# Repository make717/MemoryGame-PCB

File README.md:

# MemoryGame-PCB
KiCad PCB files for custom [Make717 memory game](https://github.com/make717gh/MemoryGame) soldering badge. This badge was designed and built by members of [Make717](https://www.make717.org) for a soldering event at the [Lancaster Science Factory](https://www.lancastersciencefactory.org/) on April 27, 2019.

This badge is using the [SAMD21G](https://cdn-shop.adafruit.com/product-files/2772/atmel-42181-sam-d21_datasheet.pdf) 32-bit microcontroller running [CircuitPython](https://github.com/make717gh/circuitpython). Thank you to [Adafruit](https://www.adafruit.com). 

# Power
The badge is powered by either USB or two AAA batteries (*SW1* "Power Switch" can be either in *USB* or *BATT*). If using batteries, ensure they are 1.5 volts and fully charged. The badge might not power up with recharable batteries which are often rated at 1.2 volts. The USB connection goes through a voltage regulator to supply 3.3 volts to the microcontroller and other components on the board.

# Ready to Build
If you are joining us at Make717, or have all the component to build a badge, you can follow the [assembling instructions](https://github.com/make717gh/MemoryGame-PCB/blob/master/ASSEMBLING.md) which include tips on what to check if the badge is not working.

# Flashing and Firmware
You can update the firmware on the badge over USB by droping an updated UF2 image when in bootloader mode. To enter this mode, double tap the *RST1* to *GND1* while powered over USB. The drive should reappear as *MAKEBOOT* when it has entered this mode. 

It is also possible to directly program the SAMD21G18A using Serial Wire Debug (SWD). We recommend a [J-LINK](https://www.adafruit.com/product/3571) programmer or similar, connecting to *SWDIO1* (data), *SWCLK1* (clock), *GND1* (ground), and *3V3* (power). You will also need to power the board with 3.3 volts which can be done via the USB connection while programming or the *5V* pin near the USB port.

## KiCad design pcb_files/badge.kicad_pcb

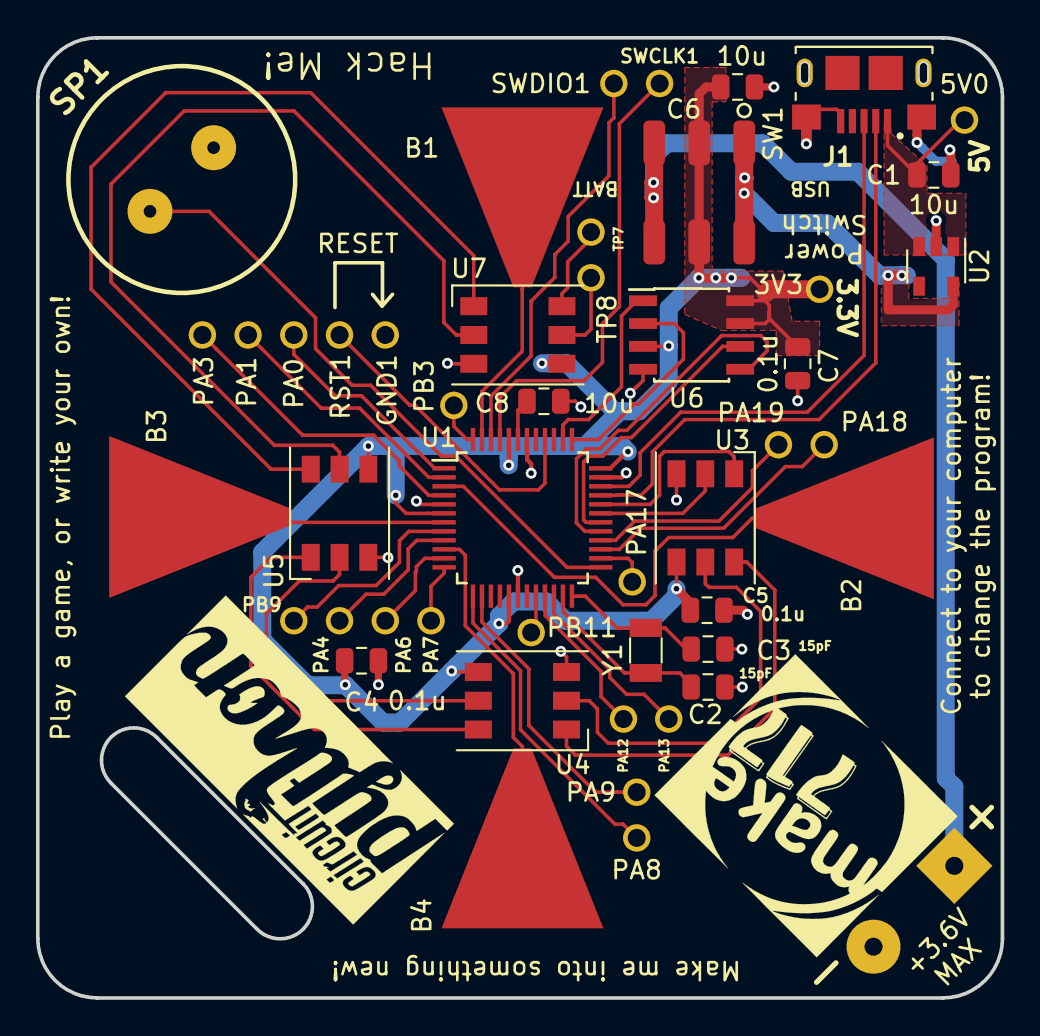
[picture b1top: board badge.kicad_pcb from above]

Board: 2 copper layers, 53.6 x 53.3 mm, 48 parts (1 on the bottom side), 48 nets.

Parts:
3V3, 5V0: TestPoint; TestPoint_THTPad_D1.5mm_Drill1.0mm
B1, B2, B3, B4: PTC_pad_badge; PTC_badge
BH1: AAA_holder; aaa_battery_holder
C1, C6, C8: 10u; C_0805_2012Metric
C2, C3: 15pF; C_0805_2012Metric
C4, C5, C7: 0.1u; C_0805_2012Metric
GND1: TestPoint; TestPoint_THTPad_D1.5mm_Drill1.0mm
J1: 10118193-0001LF; usb
PA0, PA1, PA3, PA4, PA6, PA7, PA8, PA9, PA12, PA13, PA17, PA18, PA19: TestPoint; TestPoint_THTPad_D1.5mm_Drill1.0mm
PB3, PB9, PB11: TestPoint; TestPoint_THTPad_D1.5mm_Drill1.0mm
RST1: TestPoint; TestPoint_THTPad_D1.5mm_Drill1.0mm
SP1: PKM13EPYH4000-A0; PKM13EPYH4002-B0
SW1: JS202011SCQN
SWCLK1: TestPoint; TestPoint_THTPad_D1.5mm_Drill1.0mm
SWDIO1: TestPoint; TestPoint_THTPad_D1.5mm_Drill1.0mm
TP7, TP8: TestPoint; TestPoint_THTPad_D1.5mm_Drill1.0mm
U1: ATSAMD21G18A-AUT; TQFP-48_7x7mm_P0.5mm
U2: MIC5504-3.3YM5; SOT-23-5
U3, U4, U5, U7: SK9822; LED_WS2812_PLCC6_5.0x5.0mm_P1.6mm
U6: AT25SF041-SSHD-B; SOIC-8_3.9x4.9mm_P1.27mm
Y1: Crystal; Crystal_SMD_3215-2Pin_3.2x1.5mm

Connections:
+3V3: 3V3.1, C4.1, C5.1, C6.1, C7.1, SW1.2, SW1.5, U1.6, U1.17, U1.36, U1.44, U3.4, U4.4, U5.4, U6.3, U6.7, U6.8, U7.4
/BUZZER: SP1.1, U1.25
/FLASH_CS#: U1.38, U6.1
/FLASH_SCK: U1.30, U6.6
/FLASH_SI: U1.29, U6.5
/FLASH_SO: U1.37, U6.2
/LED_CLK: U1.31, U3.2
/LED_SDI: U1.32, U3.1
/PA00: PA0.1, U1.1
/PA01: PA1.1, U1.2
/PA03: PA3.1, U1.4
/PA04: PA4.1, U1.9
/PA06: PA6.1, U1.11
/PA07: PA7.1, U1.12
/PA08: PA8.1, U1.13
/PA09: PA9.1, U1.14
/PA12: PA12.1, U1.21
/PA13: PA13.1, U1.22
/PA17: PA17.1, U1.26
/PA18: PA18.1, U1.27
/PA19: PA19.1, U1.28
/PB03: PB3.1, U1.48
/PB09: PB9.1, U1.8
/PB11: PB11.1, U1.20
/PTC_BUTTON1: B1.1, U1.47
/PTC_BUTTON2: B2.1, U1.3
/PTC_BUTTON3: B3.1, U1.7
/PTC_BUTTON4: B4.1, U1.10
/SWCLK: SWCLK1.1, U1.45
/SWDIO: SWDIO1.1, U1.46
/USBVDD_5V: 5V0.1, C1.1, J1.1, U2.1, U2.3
/USB_N: J1.2, U1.33
/USB_P: J1.3, U1.34
/XTAL1_PA14: C2.1, U1.23, Y1.1
/XTAL2_PA15: C3.1, U1.24, Y1.2
GND: BH1.2, C1.2, C2.2, C3.2, C4.2, C5.2, C6.2, C7.2, C8.2, GND1.1, J1.5, J1.S1, J1.S2, SP1.2, U1.5, U1.18, U1.35, U1.42, U2.2, U3.3, U4.3, U5.3, U6.4, U7.3
unnamed: BH1.1, SW1.3, SW1.6
unnamed: C8.1, U1.43
unnamed: RST1.1, U1.40
unnamed: SW1.1, SW1.4, U2.5
unnamed: TP7.1, U7.6
unnamed: TP8.1, U7.5
unnamed: U3.5, U4.2
unnamed: U3.6, U4.1
unnamed: U4.5, U5.2
unnamed: U4.6, U5.1
unnamed: U5.5, U7.2
unnamed: U5.6, U7.1

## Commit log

2019-02-22 PDF of schematic and top board
2019-02-22 Updated for the SAMD21G
2019-02-22 Links to useful info
2019-03-16 Testing Push
2019-03-16 including kicad files
2019-03-20 Update power and firmware info
2019-04-03 Updated Pin values for final board design
2019-04-03 Laying down some info from our session
2019-04-03 Pics and Instructions
2019-04-03 Adding heat check
2019-04-03 Update ASSEMBLING.md
    Added power switch to bullet list
2019-04-04 Firmware for pre-flashing
2019-04-13 Updated Boot name
